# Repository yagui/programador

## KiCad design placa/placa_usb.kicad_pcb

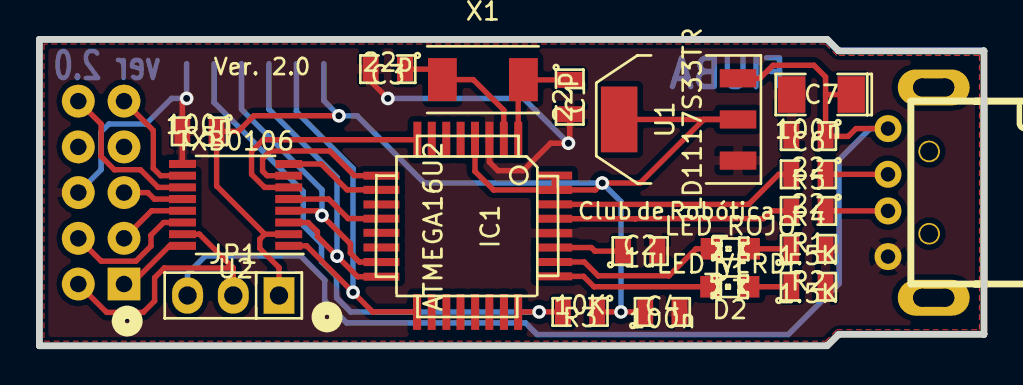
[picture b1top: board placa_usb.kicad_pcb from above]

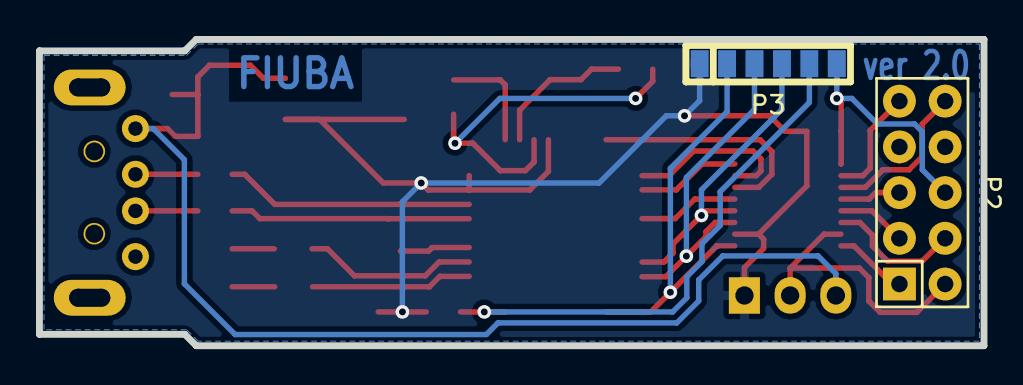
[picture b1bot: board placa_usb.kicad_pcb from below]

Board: 2 copper layers, 52.5 x 17.0 mm, 22 parts (2 on the bottom side), 29 nets.

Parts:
C1, C3: 22p; SMD-0805
C2: 1u; SMD-0805
C4, C5, C6: 100n; SMD-0805
C7: 33u; SMD-1206_Pol
D1: LED_ROJO; LED-0805
D2: LED_VERDE; LED-0805
IC1: ATMEGA16U2; TQFP-32
JP1: JUMPER3; Socket_Strip_Straight_1x03
P1: USB_A; USB_A_custom
P2: CONN_02X05; Socket_Strip_Straight_2x05
P3: CONN_01X06; Socket_Strip_smd_1x06
R1, R2: 1.5K; SMD-0805
R3: 10K; SMD-0805
R4, R5: 22; SMD-0805
U1: LD1117S33TR; SOT-223
U2: TXB0106; TSSOP-16_4.4x5mm_Pitch0.65mm
X1: 8MHz; Crystal_SMD_0603_2Pads_obsolete

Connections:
+3V3: C4.1, C5.1, IC1.4, IC1.31, IC1.32, JP1.1, P3.1, R3.1, U1.2, U2.2
+5V: C6.1, C7.1, JP1.3, P1.1, U1.3
/D+: IC1.29, R4.2
/D-: IC1.30, R5.2
/Enable: IC1.10, U2.8
/MISO: IC1.17, P3.2, U2.1
/MISO-O: P2.1, U2.16
/MOSI: IC1.16, P3.3, U2.3
/MOSI-O: P2.4, U2.14
/RESET: IC1.24, P3.5, R3.2
/RST: IC1.12, U2.5
/RST-O: P2.5, U2.12
/RX: IC1.8, U2.6
/RX-O: P2.10, U2.11
/Rojo: D1.2, IC1.26
/SCK: IC1.15, P3.4, U2.4
/SCK-O: P2.3, U2.13
/TX: IC1.9, U2.7
/TX-O: P2.9, U2.10
/VCC-O: JP1.2, P2.2, U2.15
/Verde: D2.2, IC1.25
GND: C1.2, C2.2, C3.2, C4.2, C5.2, C6.2, C7.2, IC1.3, IC1.28, P1.4, P2.6, P3.6, R1.2, R2.2, U1.1, U2.9
unnamed: C1.1, IC1.1, X1.2
unnamed: C2.1, IC1.27
unnamed: C3.1, IC1.2, X1.1
unnamed: D1.1, R1.1
unnamed: D2.1, R2.1
unnamed: P1.2, R5.1
unnamed: P1.3, R4.1

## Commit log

2015-09-19 primera version de la placa en componentes smd, queda verificar los tamaños de los footprint
